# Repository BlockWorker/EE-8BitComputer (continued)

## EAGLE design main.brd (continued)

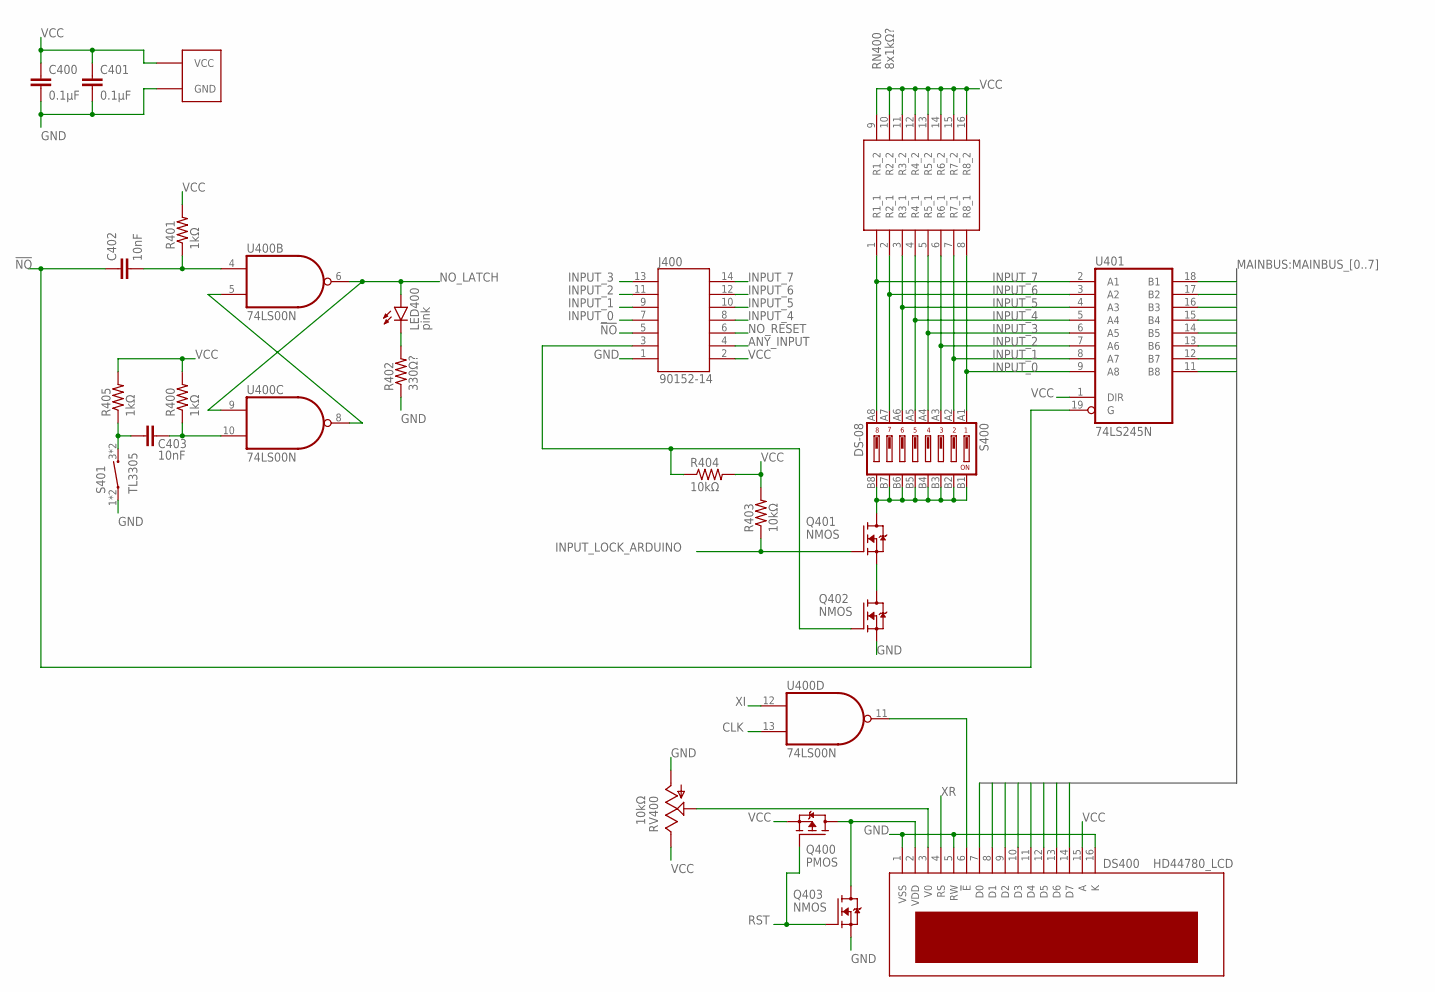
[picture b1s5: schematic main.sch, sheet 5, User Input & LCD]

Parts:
C400, C401: 0.1µF; C0805K
C402, C403: 10nF; C0805K
DS400: HD44780_LCD
J400: 90152-14
LED400: pink; LED3MM
Q400: PMOS; SOT23
Q401, Q402, Q403: NMOS; SOT23
R400, R401, R405: 1kΩ; R0805
R402: 330Ω?; R0805
R403, R404: 10kΩ; R0805
RN400: 8x1kΩ?; CAY16102J8LF
RV400: 10kΩ; CA9V
S400: DS-08; DIPSW-08
S401: TL3305; TL3305_MICROSWITCH
U400: 74LS00N; DIL14
U401: 74LS245N; DIL20

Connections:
!LCD_E: DS400.6 (!E), U400.11 (O)
!NO: C402.1, J400.5, U401.19 (G); also elsewhere on the board
!NO_LATCH: U400.5 (I1), U400.8 (O)
ANY_INPUT: J400.4; also elsewhere on the board
CLK: U400.13 (I1); also elsewhere on the board
GND: C400.2, C401.2, DS400.1 (VSS), DS400.5 (RW), DS400.16 (K), J400.1, Q402.2 (S), Q403.2 (S), R402.1, RV400.A, S401.1, S401.2 (1), U400.7 (GND), U401.10 (GND); also elsewhere on the board
INPUT_0: J400.7, RN400.8 (R8_1), S400.A1 (1), U401.9 (A8); also elsewhere on the board
INPUT_1: J400.9, RN400.7 (R7_1), S400.A2 (2), U401.8 (A7); also elsewhere on the board
INPUT_2: J400.11, RN400.6 (R6_1), S400.A3 (3), U401.7 (A6); also elsewhere on the board
INPUT_3: J400.13, RN400.5 (R5_1), S400.A4 (4), U401.6 (A5); also elsewhere on the board
INPUT_4: J400.8, RN400.4 (R4_1), S400.A5 (5), U401.5 (A4); also elsewhere on the board
INPUT_5: J400.10, RN400.3 (R3_1), S400.A6 (6), U401.4 (A3); also elsewhere on the board
INPUT_6: J400.12, RN400.2 (R2_1), S400.A7 (7), U401.3 (A2); also elsewhere on the board
INPUT_7: J400.14, RN400.1 (R1_1), S400.A8 (8), U401.2 (A1); also elsewhere on the board
INPUT_GND: Q401.3 (D), S400.B1 (16), S400.B2 (15), S400.B3 (14), S400.B4 (13), S400.B5 (12), S400.B6 (11), S400.B7 (10), S400.B8 (9)
INPUT_GND_INT: Q401.2 (S), Q402.3 (D)
INPUT_LOCK_ARDUINO: Q401.1 (G), R403.1; also elsewhere on the board
INPUT_LOCK_EXT: J400.3, Q402.1 (G), R404.1
LCD_V0: DS400.3 (V0), RV400.S
LCD_VDD: DS400.2 (VDD), Q400.3 (D), Q403.3 (D)
MAINBUS_0: DS400.7 (D0), U401.11 (B8); also elsewhere on the board
MAINBUS_1: DS400.8 (D1), U401.12 (B7); also elsewhere on the board
MAINBUS_2: DS400.9 (D2), U401.13 (B6); also elsewhere on the board
MAINBUS_3: DS400.10 (D3), U401.14 (B5); also elsewhere on the board
MAINBUS_4: DS400.11 (D4), U401.15 (B4); also elsewhere on the board
MAINBUS_5: DS400.12 (D5), U401.16 (B3); also elsewhere on the board
MAINBUS_6: DS400.13 (D6), U401.17 (B2); also elsewhere on the board
MAINBUS_7: DS400.14 (D7), U401.18 (B1); also elsewhere on the board
NO_LATCH: LED400.A, U400.6 (O), U400.9 (I0); also elsewhere on the board
NO_LED: LED400.K (C), R402.2
NO_RESET: C403.1, J400.6, R405.1, S401.3 (2), S401.4 (2); also elsewhere on the board
NO_RESET_PULSE: C403.2, R400.1, U400.10 (I1)
NO_SET_PULSE: C402.2, R401.1, U400.4 (I0)
RST: Q400.1 (G), Q403.1 (G); also elsewhere on the board
VCC: C400.1, C401.1, DS400.15 (A), J400.2, Q400.2 (S), R400.2, R401.2, R403.2, R404.2, R405.2, RN400.9 (R1_2), RN400.10 (R2_2), RN400.11 (R3_2), RN400.12 (R4_2), RN400.13 (R5_2), RN400.14 (R6_2), RN400.15 (R7_2), RN400.16 (R8_2), RV400.E, U400.14 (VCC), U401.1 (DIR), U401.20 (VCC); also elsewhere on the board
XI: U400.12 (I0); also elsewhere on the board
XR: DS400.4 (RS); also elsewhere on the board

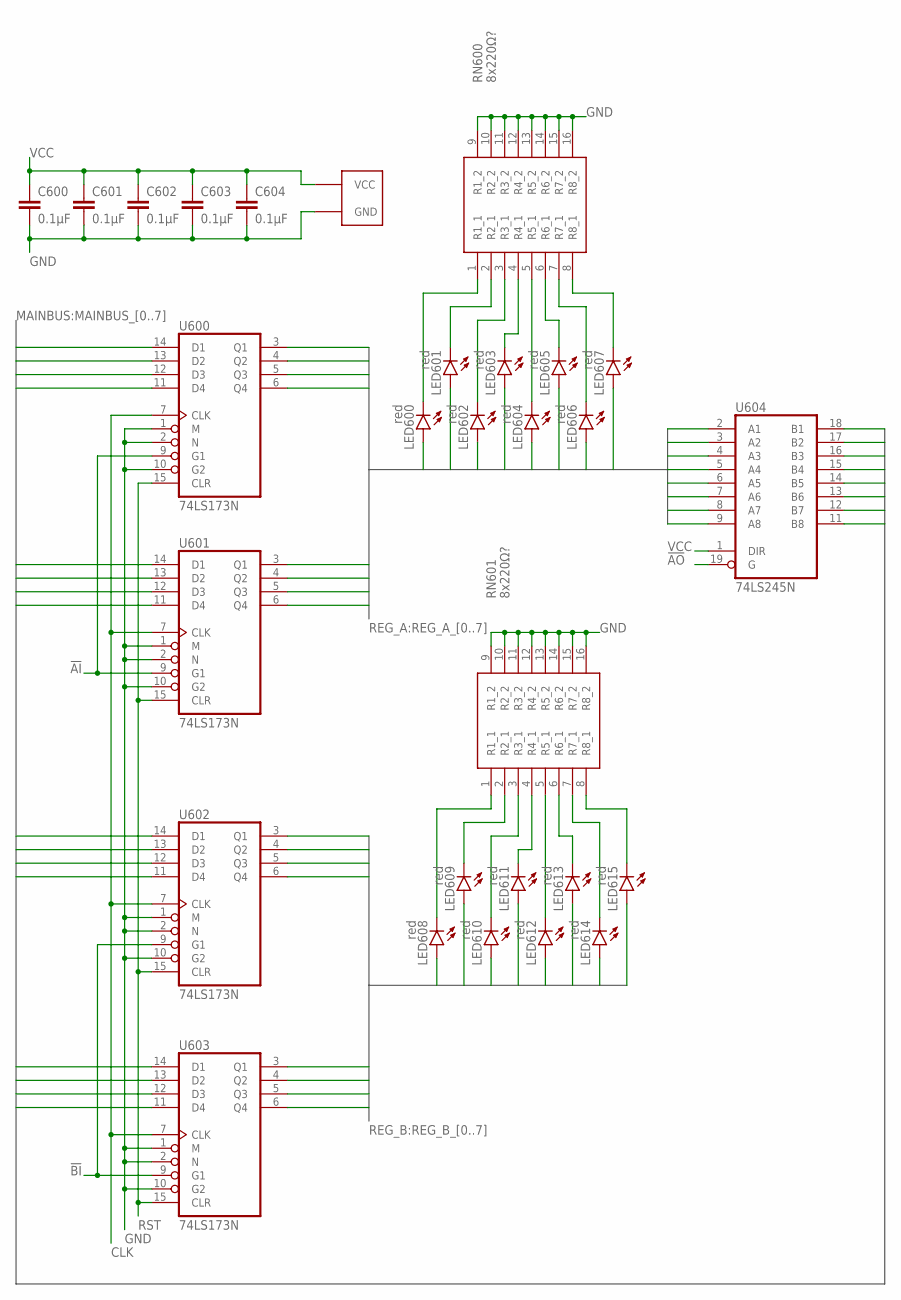
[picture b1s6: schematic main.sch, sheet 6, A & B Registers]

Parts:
C600, C601, C602, C603, C604: 0.1µF; C0805K
LED600, LED601, LED602, LED603, LED604, LED605, LED606, LED607, LED608, LED609, LED610, LED611, LED612, LED613, LED614, LED615: red; LED3MM
RN600, RN601: 8x220Ω?; CAY16102J8LF
U600, U601, U602, U603: 74LS173N; DIL16
U604: 74LS245N; DIL20

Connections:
!AI: U600.9 (G1), U601.9 (G1); also elsewhere on the board
!AO: U604.19 (G); also elsewhere on the board
!BI: U602.9 (G1), U603.9 (G1); also elsewhere on the board
CLK: U600.7 (CLK), U601.7 (CLK), U602.7 (CLK), U603.7 (CLK); also elsewhere on the board
GND: C600.2, C601.2, C602.2, C603.2, C604.2, RN600.9 (R1_2), RN600.10 (R2_2), RN600.11 (R3_2), RN600.12 (R4_2), RN600.13 (R5_2), RN600.14 (R6_2), RN600.15 (R7_2), RN600.16 (R8_2), RN601.9 (R1_2), RN601.10 (R2_2), RN601.11 (R3_2), RN601.12 (R4_2), RN601.13 (R5_2), RN601.14 (R6_2), RN601.15 (R7_2), RN601.16 (R8_2), U600.1 (M), U600.2 (N), U600.8 (GND), U600.10 (G2), U601.1 (M), U601.2 (N), U601.8 (GND), U601.10 (G2), U602.1 (M), U602.2 (N), U602.8 (GND), U602.10 (G2), U603.1 (M), U603.2 (N), U603.8 (GND), U603.10 (G2), U604.10 (GND); also elsewhere on the board
LED600_GND: LED600.K (C), RN600.1 (R1_1)
LED601_GND: LED601.K (C), RN600.2 (R2_1)
LED602_GND: LED602.K (C), RN600.3 (R3_1)
LED603_GND: LED603.K (C), RN600.4 (R4_1)
LED604_GND: LED604.K (C), RN600.5 (R5_1)
LED605_GND: LED605.K (C), RN600.6 (R6_1)
LED606_GND: LED606.K (C), RN600.7 (R7_1)
LED607_GND: LED607.K (C), RN600.8 (R8_1)
LED608_GND: LED608.K (C), RN601.1 (R1_1)
LED609_GND: LED609.K (C), RN601.2 (R2_1)
LED610_GND: LED610.K (C), RN601.3 (R3_1)
LED611_GND: LED611.K (C), RN601.4 (R4_1)
LED612_GND: LED612.K (C), RN601.5 (R5_1)
LED613_GND: LED613.K (C), RN601.6 (R6_1)
LED614_GND: LED614.K (C), RN601.7 (R7_1)
LED615_GND: LED615.K (C), RN601.8 (R8_1)
MAINBUS_0: U601.11 (D4), U603.11 (D4), U604.11 (B8); also elsewhere on the board
MAINBUS_1: U601.12 (D3), U603.12 (D3), U604.12 (B7); also elsewhere on the board
MAINBUS_2: U601.13 (D2), U603.13 (D2), U604.13 (B6); also elsewhere on the board
MAINBUS_3: U601.14 (D1), U603.14 (D1), U604.14 (B5); also elsewhere on the board
MAINBUS_4: U600.11 (D4), U602.11 (D4), U604.15 (B4); also elsewhere on the board
MAINBUS_5: U600.12 (D3), U602.12 (D3), U604.16 (B3); also elsewhere on the board
MAINBUS_6: U600.13 (D2), U602.13 (D2), U604.17 (B2); also elsewhere on the board
MAINBUS_7: U600.14 (D1), U602.14 (D1), U604.18 (B1); also elsewhere on the board
REG_A_0: LED607.A, U601.6 (Q4), U604.9 (A8); also elsewhere on the board
REG_A_1: LED606.A, U601.5 (Q3), U604.8 (A7); also elsewhere on the board
REG_A_2: LED605.A, U601.4 (Q2), U604.7 (A6); also elsewhere on the board
REG_A_3: LED604.A, U601.3 (Q1), U604.6 (A5); also elsewhere on the board
REG_A_4: LED603.A, U600.6 (Q4), U604.5 (A4); also elsewhere on the board
REG_A_5: LED602.A, U600.5 (Q3), U604.4 (A3); also elsewhere on the board
REG_A_6: LED601.A, U600.4 (Q2), U604.3 (A2); also elsewhere on the board
REG_A_7: LED600.A, U600.3 (Q1), U604.2 (A1); also elsewhere on the board
REG_B_0: LED615.A, U603.6 (Q4); also elsewhere on the board
REG_B_1: LED614.A, U603.5 (Q3); also elsewhere on the board
REG_B_2: LED613.A, U603.4 (Q2); also elsewhere on the board
REG_B_3: LED612.A, U603.3 (Q1); also elsewhere on the board
REG_B_4: LED611.A, U602.6 (Q4); also elsewhere on the board
REG_B_5: LED610.A, U602.5 (Q3); also elsewhere on the board
REG_B_6: LED609.A, U602.4 (Q2); also elsewhere on the board
REG_B_7: LED608.A, U602.3 (Q1); also elsewhere on the board
RST: U600.15 (CLR), U601.15 (CLR), U602.15 (CLR), U603.15 (CLR); also elsewhere on the board
VCC: C600.1, C601.1, C602.1, C603.1, C604.1, U600.16 (VCC), U601.16 (VCC), U602.16 (VCC), U603.16 (VCC), U604.1 (DIR), U604.20 (VCC); also elsewhere on the board

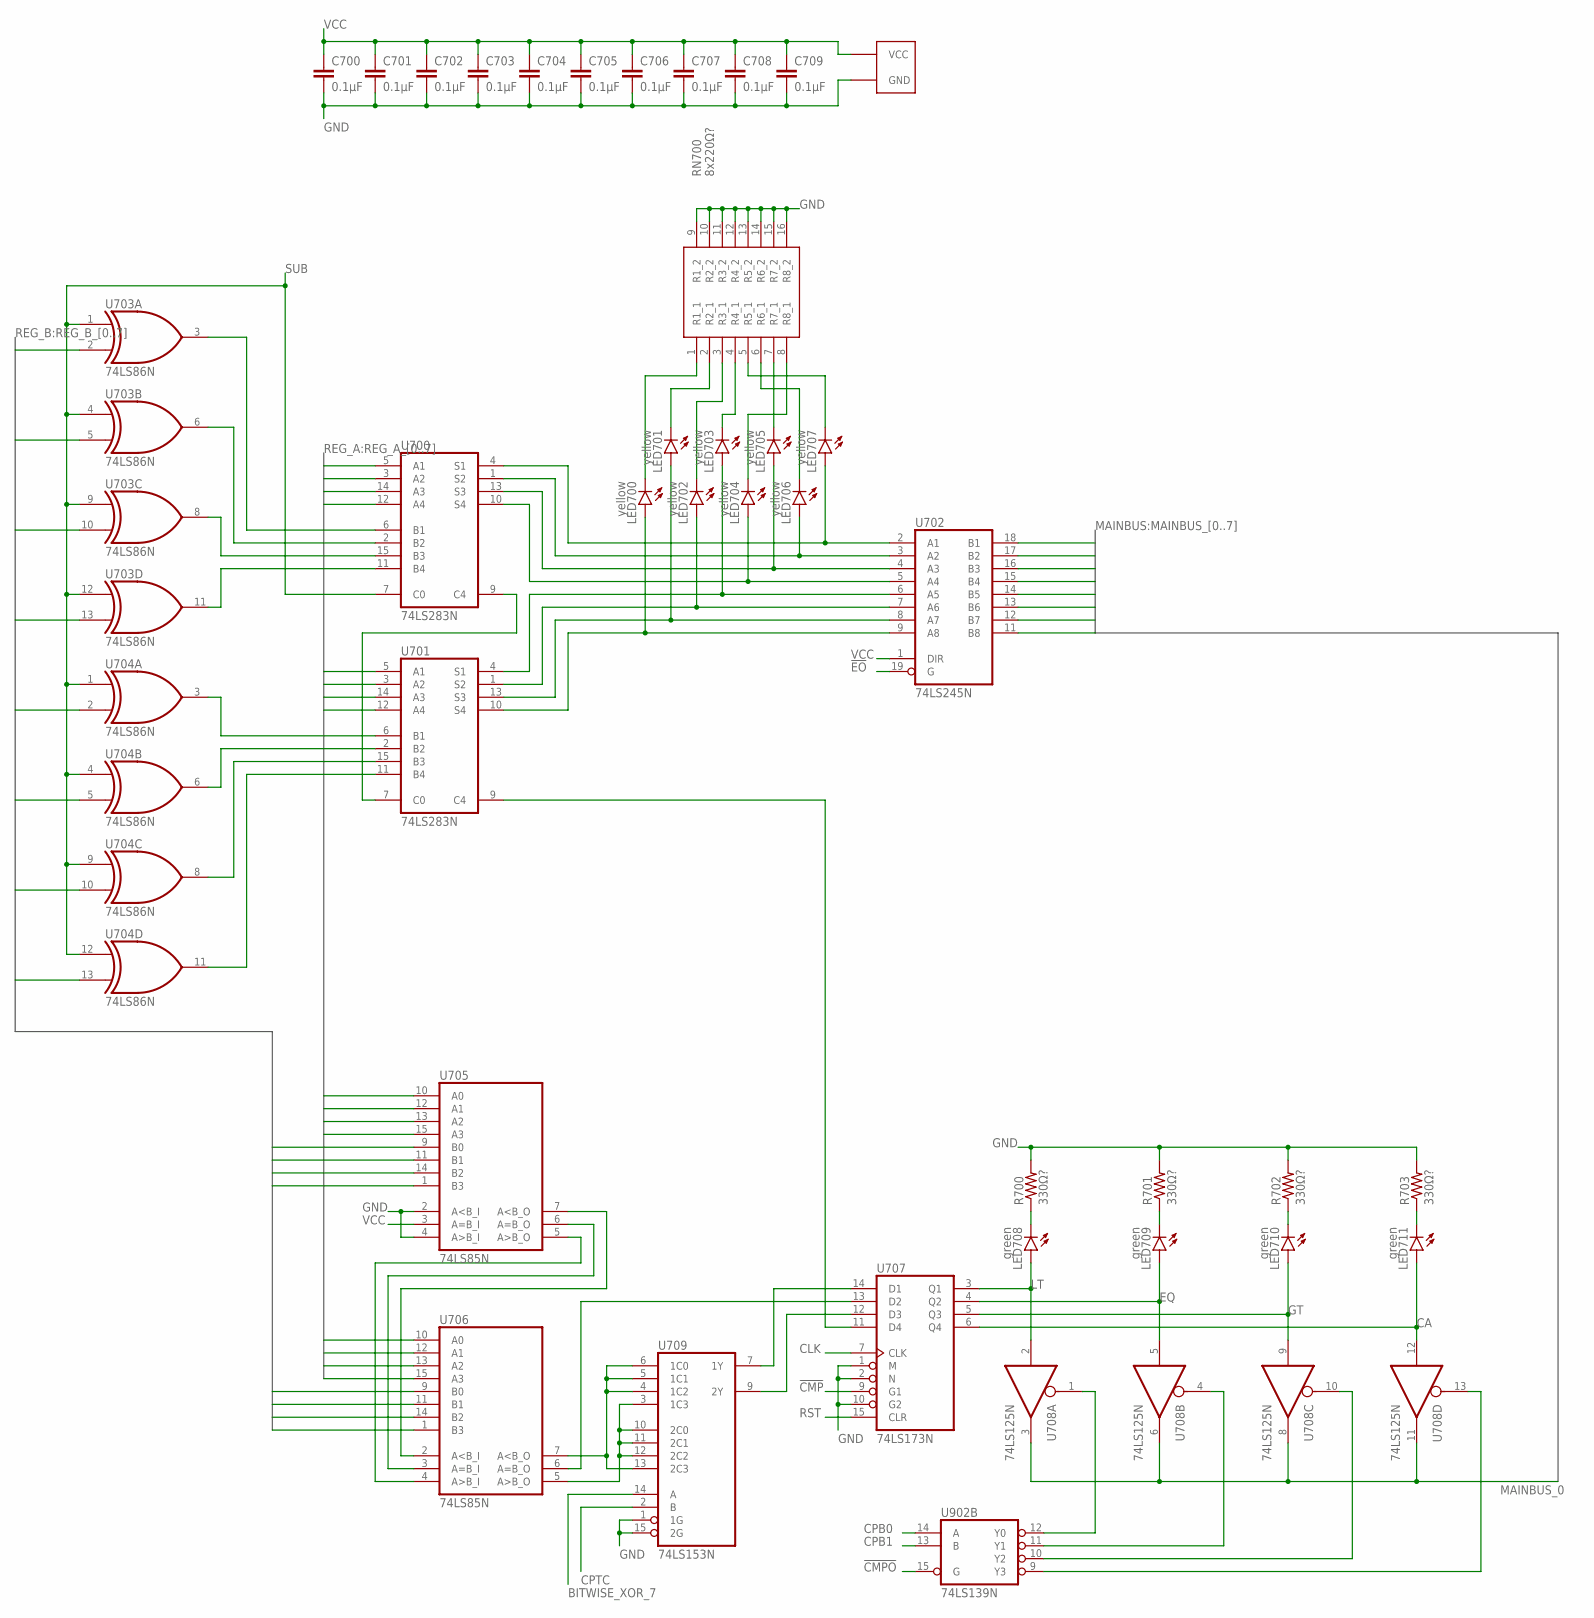
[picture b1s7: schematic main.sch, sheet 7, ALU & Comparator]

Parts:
C700, C701, C702, C703, C704, C705, C706, C707, C708, C709: 0.1µF; C0805K
LED700, LED701, LED702, LED703, LED704, LED705, LED706, LED707: yellow; LED3MM
LED708, LED709, LED710, LED711: green; LED3MM
R700, R701, R702, R703: 330Ω?; R0805
RN700: 8x220Ω?; CAY16102J8LF
U700, U701: 74LS283N; DIL16
U702: 74LS245N; DIL20
U703, U704: 74LS86N; DIL14
U705, U706: 74LS85N; DIL16
U707: 74LS173N; DIL16
U708: 74LS125N; DIL14
U709: 74LS153N; DIL16
U902: 74LS139N; DIL16

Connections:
!CMP: U707.9 (G1); also elsewhere on the board
!CMPO: U902.15 (G); also elsewhere on the board
!CMP_CA_OUT: U708.13 (OE), U902.9 (Y3)
!CMP_EQ_OUT: U708.4 (OE), U902.11 (Y1)
!CMP_GT_OUT: U708.10 (OE), U902.10 (Y2)
!CMP_LT_OUT: U708.1 (OE), U902.12 (Y0)
!EO: U702.19 (G); also elsewhere on the board
ALU_B_0: U700.6 (B1), U703.3 (O)
ALU_B_1: U700.2 (B2), U703.6 (O)
ALU_B_2: U700.15 (B3), U703.8 (O)
ALU_B_3: U700.11 (B4), U703.11 (O)
ALU_B_4: U701.6 (B1), U704.3 (O)
ALU_B_5: U701.2 (B2), U704.6 (O)
ALU_B_6: U701.15 (B3), U704.8 (O)
ALU_B_7: U701.11 (B4), U704.11 (O)
ALU_CARRY_OVER: U701.9 (C4), U707.11 (D4)
ALU_INT_CARRY: U700.9 (C4), U701.7 (C0)
ALU_SUM_0: LED707.A, U700.4 (S1), U702.2 (A1)
ALU_SUM_1: LED706.A, U700.1 (S2), U702.3 (A2)
ALU_SUM_2: LED705.A, U700.13 (S3), U702.4 (A3)
ALU_SUM_3: LED704.A, U700.10 (S4), U702.5 (A4)
ALU_SUM_4: LED703.A, U701.4 (S1), U702.6 (A5)
ALU_SUM_5: LED702.A, U701.1 (S2), U702.7 (A6)
ALU_SUM_6: LED701.A, U701.13 (S3), U702.8 (A7)
ALU_SUM_7: LED700.A, U701.10 (S4), U702.9 (A8)
BITWISE_XOR_7: U709.14 (A); also elsewhere on the board
CA: LED711.A, U707.6 (Q4), U708.12 (I)
CLK: U707.7 (CLK); also elsewhere on the board
CMP_<_CARRY: U705.7 (A<B_O), U706.2 (A<B_I)
CMP_=_CARRY: U705.6 (A=B_O), U706.3 (A=B_I)
CMP_>_CARRY: U705.5 (A>B_O), U706.4 (A>B_I)
CMP_EQ_INT: U706.6 (A=B_O), U707.13 (D2)
CMP_GT_INT: U707.12 (D3), U709.9 (2Y)
CMP_GT_PRE: U706.5 (A>B_O), U709.3 (1C3), U709.10 (2C0), U709.11 (2C1), U709.12 (2C2)
CMP_LT_INT: U707.14 (D1), U709.7 (1Y)
CMP_LT_PRE: U706.7 (A<B_O), U709.4 (1C2), U709.5 (1C1), U709.6 (1C0), U709.13 (2C3)
CPB0: U902.14 (A); also elsewhere on the board
CPB1: U902.13 (B); also elsewhere on the board
CPTC: U709.2 (B); also elsewhere on the board
EQ: LED709.A, U707.4 (Q2), U708.5 (I)
GND: C700.2, C701.2, C702.2, C703.2, C704.2, C705.2, C706.2, C707.2, C708.2, C709.2, R700.2, R701.2, R702.2, R703.2, RN700.9 (R1_2), RN700.10 (R2_2), RN700.11 (R3_2), RN700.12 (R4_2), RN700.13 (R5_2), RN700.14 (R6_2), RN700.15 (R7_2), RN700.16 (R8_2), U700.8 (GND), U701.8 (GND), U702.10 (GND), U703.7 (GND), U704.7 (GND), U705.2 (A<B_I), U705.4 (A>B_I), U705.8 (GND), U706.8 (GND), U707.1 (M), U707.2 (N), U707.8 (GND), U707.10 (G2), U708.7 (GND), U709.1 (1G), U709.8 (GND), U709.15 (2G), U902.8 (GND); also elsewhere on the board
GT: LED710.A, U707.5 (Q3), U708.9 (I); also elsewhere on the board
LED700_GND: LED700.K (C), RN700.1 (R1_1)
LED701_GND: LED701.K (C), RN700.2 (R2_1)
LED702_GND: LED702.K (C), RN700.3 (R3_1)
LED703_GND: LED703.K (C), RN700.4 (R4_1)
LED704_GND: LED704.K (C), RN700.8 (R8_1)
LED705_GND: LED705.K (C), RN700.7 (R7_1)
LED706_GND: LED706.K (C), RN700.6 (R6_1)
LED707_GND: LED707.K (C), RN700.5 (R5_1)
LED708_GND: LED708.K (C), R700.1
LED709_GND: LED709.K (C), R701.1
LED710_GND: LED710.K (C), R702.1
LED711_GND: LED711.K (C), R703.1
LT: LED708.A, U707.3 (Q1), U708.2 (I); also elsewhere on the board
MAINBUS_0: U702.18 (B1), U708.3 (O), U708.6 (O), U708.8 (O), U708.11 (O); also elsewhere on the board
MAINBUS_1: U702.17 (B2); also elsewhere on the board
MAINBUS_2: U702.16 (B3); also elsewhere on the board
MAINBUS_3: U702.15 (B4); also elsewhere on the board
MAINBUS_4: U702.14 (B5); also elsewhere on the board
MAINBUS_5: U702.13 (B6); also elsewhere on the board
MAINBUS_6: U702.12 (B7); also elsewhere on the board
MAINBUS_7: U702.11 (B8); also elsewhere on the board
REG_A_0: U700.5 (A1), U705.10 (A0); also elsewhere on the board
REG_A_1: U700.3 (A2), U705.12 (A1); also elsewhere on the board
REG_A_2: U700.14 (A3), U705.13 (A2); also elsewhere on the board
REG_A_3: U700.12 (A4), U705.15 (A3); also elsewhere on the board
REG_A_4: U701.5 (A1), U706.10 (A0); also elsewhere on the board
REG_A_5: U701.3 (A2), U706.12 (A1); also elsewhere on the board
REG_A_6: U701.14 (A3), U706.13 (A2); also elsewhere on the board
REG_A_7: U701.12 (A4), U706.15 (A3); also elsewhere on the board
REG_B_0: U703.2 (I1), U705.9 (B0); also elsewhere on the board
REG_B_1: U703.5 (I1), U705.11 (B1); also elsewhere on the board
REG_B_2: U703.10 (I1), U705.14 (B2); also elsewhere on the board
REG_B_3: U703.13 (I1), U705.1 (B3); also elsewhere on the board
REG_B_4: U704.2 (I1), U706.9 (B0); also elsewhere on the board
REG_B_5: U704.5 (I1), U706.11 (B1); also elsewhere on the board
REG_B_6: U704.10 (I1), U706.14 (B2); also elsewhere on the board
REG_B_7: U704.13 (I1), U706.1 (B3); also elsewhere on the board
RST: U707.15 (CLR); also elsewhere on the board
SUB: U700.7 (C0), U703.1 (I0), U703.4 (I0), U703.9 (I0), U703.12 (I0), U704.1 (I0), U704.4 (I0), U704.9 (I0), U704.12 (I0); also elsewhere on the board
VCC: C700.1, C701.1, C702.1, C703.1, C704.1, C705.1, C706.1, C707.1, C708.1, C709.1, U700.16 (VCC), U701.16 (VCC), U702.1 (DIR), U702.20 (VCC), U703.14 (VCC), U704.14 (VCC), U705.3 (A=B_I), U705.16 (VCC), U706.16 (VCC), U707.16 (VCC), U708.14 (VCC), U709.16 (VCC), U902.16 (VCC); also elsewhere on the board

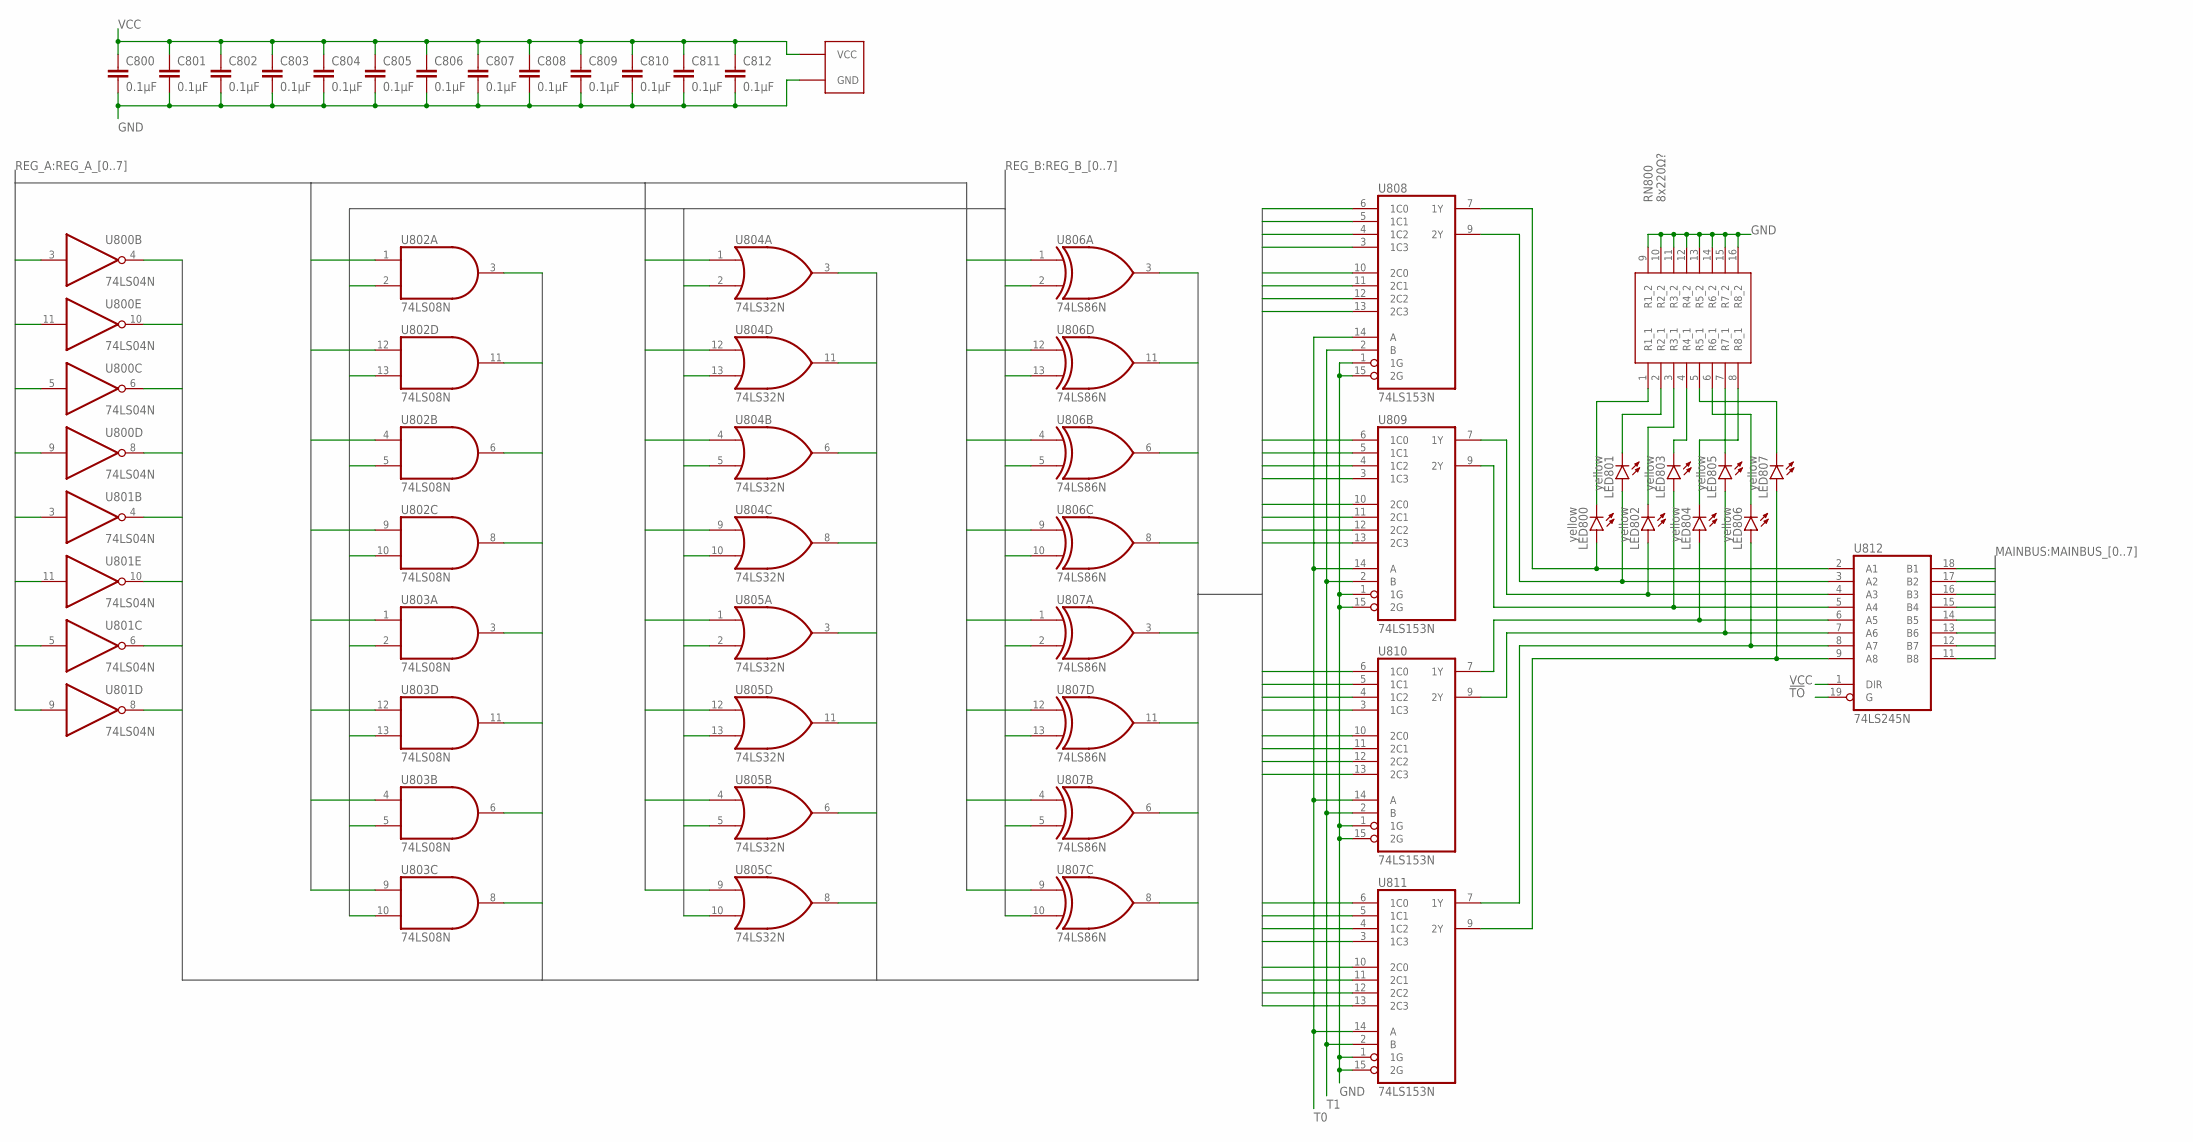
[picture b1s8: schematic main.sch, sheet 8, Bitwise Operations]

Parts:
C800, C801, C802, C803, C804, C805, C806, C807, C808, C809, C810, C811, C812: 0.1µF; C0805K
LED800, LED801, LED802, LED803, LED804, LED805, LED806, LED807: yellow; LED3MM
RN800: 8x220Ω?; CAY16102J8LF
U800, U801: 74LS04N; DIL14
U802, U803: 74LS08N; DIL14
U804, U805: 74LS32N; DIL14
U806, U807: 74LS86N; DIL14
U808, U809, U810, U811: 74LS153N; DIL16
U812: 74LS245N; DIL20

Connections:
!TO: U812.19 (G); also elsewhere on the board
BITWISE_AND_0: U803.8 (O), U811.11 (2C1)
BITWISE_AND_1: U803.6 (O), U811.5 (1C1)
BITWISE_AND_2: U803.11 (O), U810.11 (2C1)
BITWISE_AND_3: U803.3 (O), U810.5 (1C1)
BITWISE_AND_4: U802.8 (O), U809.11 (2C1)
BITWISE_AND_5: U802.6 (O), U809.5 (1C1)
BITWISE_AND_6: U802.11 (O), U808.11 (2C1)
BITWISE_AND_7: U802.3 (O), U808.5 (1C1)
BITWISE_NOT_0: U801.8 (O), U811.10 (2C0)
BITWISE_NOT_1: U801.6 (O), U811.6 (1C0)
BITWISE_NOT_2: U801.10 (O), U810.10 (2C0)
BITWISE_NOT_3: U801.4 (O), U810.6 (1C0)
BITWISE_NOT_4: U800.8 (O), U809.10 (2C0)
BITWISE_NOT_5: U800.6 (O), U809.6 (1C0)
BITWISE_NOT_6: U800.10 (O), U808.10 (2C0)
BITWISE_NOT_7: U800.4 (O), U808.6 (1C0)
BITWISE_OR_0: U805.8 (O), U811.12 (2C2)
BITWISE_OR_1: U805.6 (O), U811.4 (1C2)
BITWISE_OR_2: U805.11 (O), U810.12 (2C2)
BITWISE_OR_3: U805.3 (O), U810.4 (1C2)
BITWISE_OR_4: U804.8 (O), U809.12 (2C2)
BITWISE_OR_5: U804.6 (O), U809.4 (1C2)
BITWISE_OR_6: U804.11 (O), U808.12 (2C2)
BITWISE_OR_7: U804.3 (O), U808.4 (1C2)
BITWISE_OUT_0: LED807.A, U811.9 (2Y), U812.9 (A8)
BITWISE_OUT_1: LED806.A, U811.7 (1Y), U812.8 (A7)
BITWISE_OUT_2: LED805.A, U810.9 (2Y), U812.7 (A6)
BITWISE_OUT_3: LED804.A, U810.7 (1Y), U812.6 (A5)
BITWISE_OUT_4: LED803.A, U809.9 (2Y), U812.5 (A4)
BITWISE_OUT_5: LED802.A, U809.7 (1Y), U812.4 (A3)
BITWISE_OUT_6: LED801.A, U808.9 (2Y), U812.3 (A2)
BITWISE_OUT_7: LED800.A, U808.7 (1Y), U812.2 (A1)
BITWISE_XOR_0: U807.8 (O), U811.13 (2C3)
BITWISE_XOR_1: U807.6 (O), U811.3 (1C3)
BITWISE_XOR_2: U807.11 (O), U810.13 (2C3)
BITWISE_XOR_3: U807.3 (O), U810.3 (1C3)
BITWISE_XOR_4: U806.8 (O), U809.13 (2C3)
BITWISE_XOR_5: U806.6 (O), U809.3 (1C3)
BITWISE_XOR_6: U806.11 (O), U808.13 (2C3)
BITWISE_XOR_7: U806.3 (O), U808.3 (1C3); also elsewhere on the board
GND: C800.2, C801.2, C802.2, C803.2, C804.2, C805.2, C806.2, C807.2, C808.2, C809.2, C810.2, C811.2, C812.2, RN800.9 (R1_2), RN800.10 (R2_2), RN800.11 (R3_2), RN800.12 (R4_2), RN800.13 (R5_2), RN800.14 (R6_2), RN800.15 (R7_2), RN800.16 (R8_2), U800.7 (GND), U801.7 (GND), U802.7 (GND), U803.7 (GND), U804.7 (GND), U805.7 (GND), U806.7 (GND), U807.7 (GND), U808.1 (1G), U808.8 (GND), U808.15 (2G), U809.1 (1G), U809.8 (GND), U809.15 (2G), U810.1 (1G), U810.8 (GND), U810.15 (2G), U811.1 (1G), U811.8 (GND), U811.15 (2G), U812.10 (GND); also elsewhere on the board
LED800_GND: LED800.K (C), RN800.1 (R1_1)
LED801_GND: LED801.K (C), RN800.2 (R2_1)
LED802_GND: LED802.K (C), RN800.3 (R3_1)
LED803_GND: LED803.K (C), RN800.4 (R4_1)
LED804_GND: LED804.K (C), RN800.8 (R8_1)
LED805_GND: LED805.K (C), RN800.7 (R7_1)
LED806_GND: LED806.K (C), RN800.6 (R6_1)
LED807_GND: LED807.K (C), RN800.5 (R5_1)
MAINBUS_0: U812.11 (B8); also elsewhere on the board
MAINBUS_1: U812.12 (B7); also elsewhere on the board
MAINBUS_2: U812.13 (B6); also elsewhere on the board
MAINBUS_3: U812.14 (B5); also elsewhere on the board
MAINBUS_4: U812.15 (B4); also elsewhere on the board
MAINBUS_5: U812.16 (B3); also elsewhere on the board
MAINBUS_6: U812.17 (B2); also elsewhere on the board
MAINBUS_7: U812.18 (B1); also elsewhere on the board
REG_A_0: U801.9 (I), U803.9 (I0), U805.9 (I0), U807.9 (I0); also elsewhere on the board
REG_A_1: U801.5 (I), U803.4 (I0), U805.4 (I0), U807.4 (I0); also elsewhere on the board
REG_A_2: U801.11 (I), U803.12 (I0), U805.12 (I0), U807.12 (I0); also elsewhere on the board
REG_A_3: U801.3 (I), U803.1 (I0), U805.1 (I0), U807.1 (I0); also elsewhere on the board
REG_A_4: U800.9 (I), U802.9 (I0), U804.9 (I0), U806.9 (I0); also elsewhere on the board
REG_A_5: U800.5 (I), U802.4 (I0), U804.4 (I0), U806.4 (I0); also elsewhere on the board
REG_A_6: U800.11 (I), U802.12 (I0), U804.12 (I0), U806.12 (I0); also elsewhere on the board
REG_A_7: U800.3 (I), U802.1 (I0), U804.1 (I0), U806.1 (I0); also elsewhere on the board
REG_B_0: U803.10 (I1), U805.10 (I1), U807.10 (I1); also elsewhere on the board
REG_B_1: U803.5 (I1), U805.5 (I1), U807.5 (I1); also elsewhere on the board
REG_B_2: U803.13 (I1), U805.13 (I1), U807.13 (I1); also elsewhere on the board
REG_B_3: U803.2 (I1), U805.2 (I1), U807.2 (I1); also elsewhere on the board
REG_B_4: U802.10 (I1), U804.10 (I1), U806.10 (I1); also elsewhere on the board
REG_B_5: U802.5 (I1), U804.5 (I1), U806.5 (I1); also elsewhere on the board
REG_B_6: U802.13 (I1), U804.13 (I1), U806.13 (I1); also elsewhere on the board
REG_B_7: U802.2 (I1), U804.2 (I1), U806.2 (I1); also elsewhere on the board
T0: U808.14 (A), U809.14 (A), U810.14 (A), U811.14 (A); also elsewhere on the board
T1: U808.2 (B), U809.2 (B), U810.2 (B), U811.2 (B); also elsewhere on the board
VCC: C800.1, C801.1, C802.1, C803.1, C804.1, C805.1, C806.1, C807.1, C808.1, C809.1, C810.1, C811.1, C812.1, U800.14 (VCC), U801.14 (VCC), U802.14 (VCC), U803.14 (VCC), U804.14 (VCC), U805.14 (VCC), U806.14 (VCC), U807.14 (VCC), U808.16 (VCC), U809.16 (VCC), U810.16 (VCC), U811.16 (VCC), U812.1 (DIR), U812.20 (VCC); also elsewhere on the board

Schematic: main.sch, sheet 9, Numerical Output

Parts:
C900, C901, C902, C903, C904, C905, C906: 0.1µF; C0805K
C907, C908: 10nF; C0805K
DS900, DS901, DS902, DS903: LED_7SEG_CC; LED_7SEG
LED900, LED901, LED902: green; LED3MM
R900: 1kΩ; R0805
R901: 100kΩ; R0805
R902, R903, R904: 330Ω?; R0805
RN900: 8x220Ω?; CAY16102J8LF
U900: NE555N; DIL08
U901: 74LS161N; DIL16
U902: 74LS139N; DIL16
U903, U904, U906: 74LS173N; DIL16
XU905: AT28C64B; DIL28

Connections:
!OI: U903.9 (G1), U904.9 (G1); also elsewhere on the board
!OMI: U906.9 (G1); also elsewhere on the board
CLK: U903.7 (CLK), U904.7 (CLK), U906.7 (CLK); also elsewhere on the board
GND: C900.2, C901.2, C902.2, C903.2, C904.2, C905.2, C906.2, C907.2, C908.2, R902.1, R903.1, R904.1, U900.1 (GND), U901.8 (GND), U902.1 (G), U902.8 (GND), U903.1 (M), U903.2 (N), U903.8 (GND), U903.10 (G2), U904.1 (M), U904.2 (N), U904.8 (GND), U904.10 (G2), U906.1 (M), U906.2 (N), U906.8 (GND), U906.10 (G2), U906.11 (D4), XU905.14 (GND), XU905.20 (!CE), XU905.22 (!OE); also elsewhere on the board
LED900_GND: LED900.K (C), R902.2
LED901_GND: LED901.K (C), R903.2
LED902_GND: LED902.K (C), R904.2
MAINBUS_0: U903.14 (D1), U906.14 (D1); also elsewhere on the board
MAINBUS_1: U903.13 (D2), U906.13 (D2); also elsewhere on the board
MAINBUS_2: U903.12 (D3), U906.12 (D3); also elsewhere on the board
MAINBUS_3: U903.11 (D4); also elsewhere on the board
MAINBUS_4: U904.14 (D1); also elsewhere on the board
MAINBUS_5: U904.13 (D2); also elsewhere on the board
MAINBUS_6: U904.12 (D3); also elsewhere on the board
MAINBUS_7: U904.11 (D4); also elsewhere on the board
OUT_CAT_0: DS900.3 (CAT), DS900.8 (CAT), U902.4 (Y0)
OUT_CAT_1: DS901.3 (CAT), DS901.8 (CAT), U902.5 (Y1)
OUT_CAT_2: DS902.3 (CAT), DS902.8 (CAT), U902.6 (Y2)
OUT_CAT_3: DS903.3 (CAT), DS903.8 (CAT), U902.7 (Y3)
OUT_DATA_0: U903.3 (Q1), XU905.10 (A0)
OUT_DATA_1: U903.4 (Q2), XU905.9 (A1)
OUT_DATA_2: U903.5 (Q3), XU905.8 (A2)
OUT_DATA_3: U903.6 (Q4), XU905.7 (A3)
OUT_DATA_4: U904.3 (Q1), XU905.6 (A4)
OUT_DATA_5: U904.4 (Q2), XU905.5 (A5)
OUT_DATA_6: U904.5 (Q3), XU905.4 (A6)
OUT_DATA_7: U904.6 (Q4), XU905.3 (A7)
OUT_MODE_0: LED902.A, U906.3 (Q1), XU905.21 (A10)
OUT_MODE_1: LED901.A, U906.4 (Q2), XU905.23 (A11)
OUT_MODE_2: LED900.A, U906.5 (Q3), XU905.2 (A12)
OUT_MUX_0: U901.14 (QA), U902.2 (A), XU905.25 (A8)
OUT_MUX_1: U901.13 (QB), U902.3 (B), XU905.24 (A9)
OUT_MUX_CLK: U900.3 (Q), U901.2 (CLK)
OUT_SEG_A: DS900.7 (A), DS901.7 (A), DS902.7 (A), DS903.7 (A), RN900.9 (R1_2)
OUT_SEG_A_INT: RN900.1 (R1_1), XU905.11 (D0)
OUT_SEG_B: DS900.6 (B), DS901.6 (B), DS902.6 (B), DS903.6 (B), RN900.10 (R2_2)
OUT_SEG_B_INT: RN900.2 (R2_1), XU905.12 (D1)
OUT_SEG_C: DS900.4 (C), DS901.4 (C), DS902.4 (C), DS903.4 (C), RN900.11 (R3_2)
OUT_SEG_C_INT: RN900.3 (R3_1), XU905.13 (D2)
OUT_SEG_D: DS900.2 (D), DS901.2 (D), DS902.2 (D), DS903.2 (D), RN900.12 (R4_2)
OUT_SEG_DP: DS900.5 (DP), DS901.5 (DP), DS902.5 (DP), DS903.5 (DP), RN900.16 (R8_2)
OUT_SEG_DP_INT: RN900.8 (R8_1), XU905.19 (D7)
OUT_SEG_D_INT: RN900.4 (R4_1), XU905.15 (D3)
OUT_SEG_E: DS900.1 (E), DS901.1 (E), DS902.1 (E), DS903.1 (E), RN900.13 (R5_2)
OUT_SEG_E_INT: RN900.5 (R5_1), XU905.16 (D4)
OUT_SEG_F: DS900.9 (F), DS901.9 (F), DS902.9 (F), DS903.9 (F), RN900.14 (R6_2)
OUT_SEG_F_INT: RN900.6 (R6_1), XU905.17 (D5)
OUT_SEG_G: DS900.10 (G), DS901.10 (G), DS902.10 (G), DS903.10 (G), RN900.15 (R7_2)
OUT_SEG_G_INT: RN900.7 (R7_1), XU905.18 (D6)
RST: U903.15 (CLR), U904.15 (CLR), U906.15 (CLR); also elsewhere on the board
U900_CAP: C907.1, R901.2, U900.2 (TR), U900.6 (THR)
U900_CV: C908.1, U900.5 (CV)
U900_DIS: R900.2, R901.1, U900.7 (DIS)
VCC: C900.1, C901.1, C902.1, C903.1, C904.1, C905.1, C906.1, R900.1, U900.4 (R), U900.8 (V+), U901.1 (CLR), U901.3 (A), U901.4 (B), U901.5 (C), U901.6 (D), U901.7 (ENP), U901.9 (LD), U901.10 (ENT), U901.16 (VCC), U902.16 (VCC), U903.16 (VCC), U904.16 (VCC), U906.16 (VCC), XU905.27 (!WE), XU905.28 (VCC); also elsewhere on the board
